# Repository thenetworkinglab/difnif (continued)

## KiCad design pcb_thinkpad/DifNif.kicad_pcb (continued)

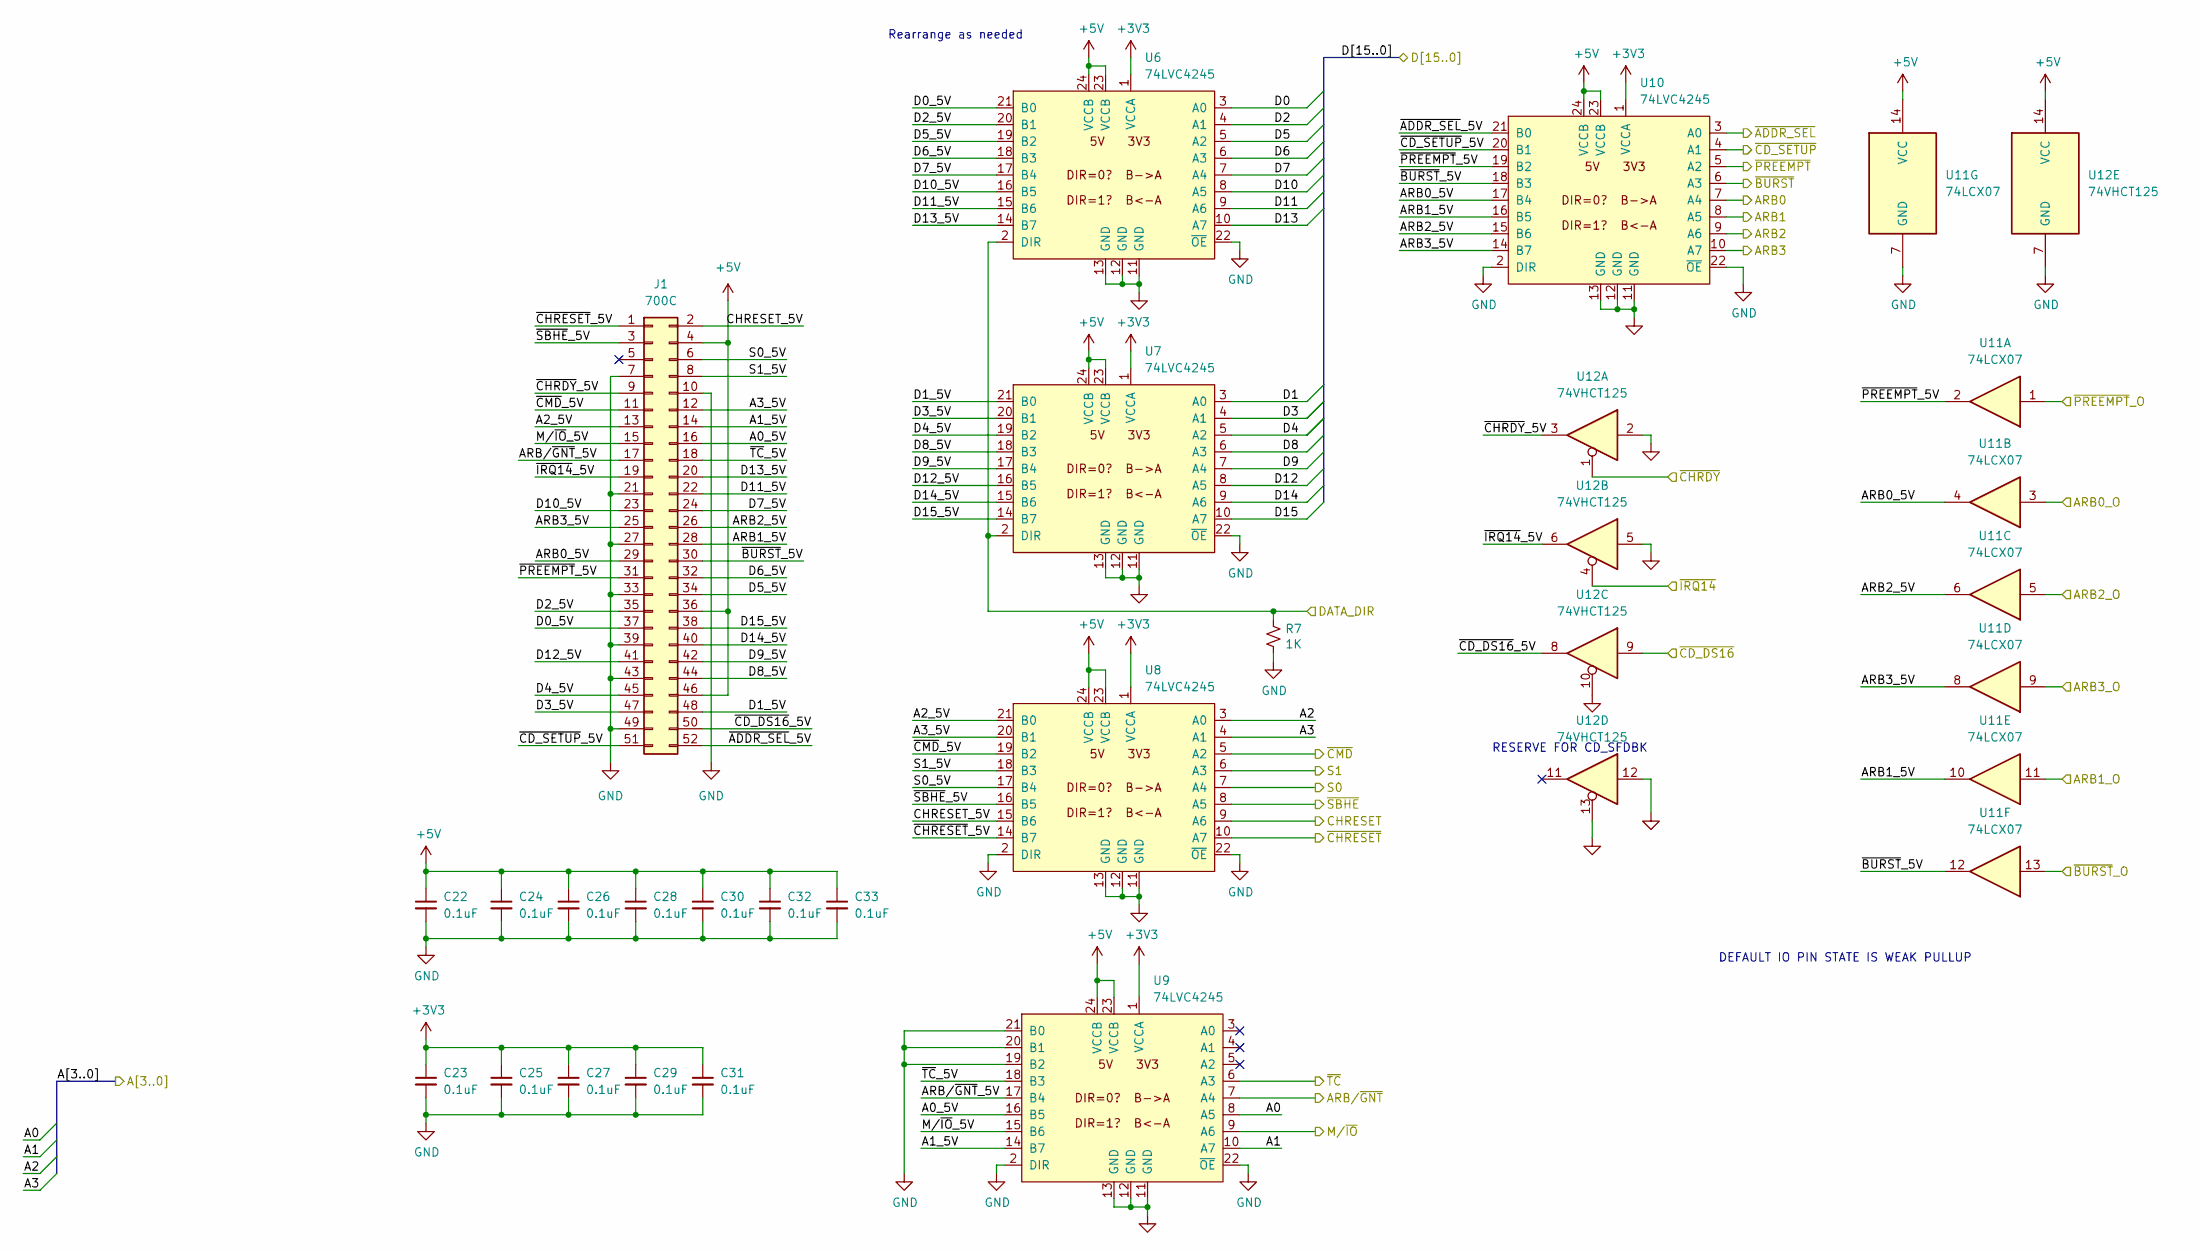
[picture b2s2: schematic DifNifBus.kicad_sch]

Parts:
C22, C23, C24, C25, C26, C27, C28, C29, C30, C31, C32, C33: 0.1uF; CAPC1608X100
J1: 700C; PinHeader_2x26_P2.00mm_Vertical
R7: 1K; RESC1608X55; Mouser 603-RC0603FR-071KL
U6, U7, U8, U9, U10: 74LVC4245; TSOP65P640X120-24; Mouser 771-74LVC4245APW-T
U11: 74LCX07; TSOP65P640X110-14; Mouser 757-74LCX07FTAE
U12: 74VHCT125; TSOP65P640X110-14; Mouser 757-74VHCT125AFT

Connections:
+3V3: C23.1, C25.1, C27.1, C29.1, C31.1, U6.1 (VCCA), U7.1 (VCCA), U8.1 (VCCA), U9.1 (VCCA), U10.1 (VCCA); also elsewhere on the board
+5V: C22.1, C24.1, C26.1, C28.1, C30.1, C32.1, C33.1, J1.4, J1.36, J1.46, U6.23 (VCCB), U6.24 (VCCB), U7.23 (VCCB), U7.24 (VCCB), U8.23 (VCCB), U8.24 (VCCB), U9.23 (VCCB), U9.24 (VCCB), U10.23 (VCCB), U10.24 (VCCB), U11.14 (VCC), U12.14 (VCC); also elsewhere on the board
/A0: U9.8 (A5); also elsewhere on the board
/A1: U9.10 (A7); also elsewhere on the board
/A2: U8.3 (A0); also elsewhere on the board
/A3: U8.4 (A1); also elsewhere on the board
/ARB0: U10.7 (A4); also elsewhere on the board
/ARB0_O: U11.3; also elsewhere on the board
/ARB1: U10.8 (A5); also elsewhere on the board
/ARB1_O: U11.11; also elsewhere on the board
/ARB2: U10.9 (A6); also elsewhere on the board
/ARB2_O: U11.5; also elsewhere on the board
/ARB3: U10.10 (A7); also elsewhere on the board
/ARB3_O: U11.9; also elsewhere on the board
/ARB/~GNT: U9.7 (A4); also elsewhere on the board
/CHRESET: U8.9 (A6); also elsewhere on the board
/D0: U6.3 (A0); also elsewhere on the board
/D1: U7.3 (A0); also elsewhere on the board
/D2: U6.4 (A1); also elsewhere on the board
/D3: U7.4 (A1); also elsewhere on the board
/D4: U7.5 (A2); also elsewhere on the board
/D5: U6.5 (A2); also elsewhere on the board
/D6: U6.6 (A3); also elsewhere on the board
/D7: U6.7 (A4); also elsewhere on the board
/D8: U7.6 (A3); also elsewhere on the board
/D9: U7.7 (A4); also elsewhere on the board
/D10: U6.8 (A5); also elsewhere on the board
/D11: U6.9 (A6); also elsewhere on the board
/D12: U7.8 (A5); also elsewhere on the board
/D13: U6.10 (A7); also elsewhere on the board
/D14: U7.9 (A6); also elsewhere on the board
/D15: U7.10 (A7); also elsewhere on the board
/DATA_DIR: R7.1, U6.2 (DIR), U7.2 (DIR); also elsewhere on the board
/DifNifBus/A0_5V: J1.16, U9.16 (B5)
/DifNifBus/A1_5V: J1.14, U9.14 (B7)
/DifNifBus/A2_5V: J1.13, U8.21 (B0)
/DifNifBus/A3_5V: J1.12, U8.20 (B1)
/DifNifBus/ARB0_5V: J1.29, U10.17 (B4), U11.4
/DifNifBus/ARB1_5V: J1.28, U10.16 (B5), U11.10
/DifNifBus/ARB2_5V: J1.26, U10.15 (B6), U11.6
/DifNifBus/ARB3_5V: J1.25, U10.14 (B7), U11.8
/DifNifBus/ARB/~GNT_5V: J1.17, U9.17 (B4)
/DifNifBus/CHRESET_5V: J1.2, U8.15 (B6)
/DifNifBus/D0_5V: J1.37, U6.21 (B0)
/DifNifBus/D1_5V: J1.48, U7.21 (B0)
/DifNifBus/D2_5V: J1.35, U6.20 (B1)
/DifNifBus/D3_5V: J1.47, U7.20 (B1)
/DifNifBus/D4_5V: J1.45, U7.19 (B2)
/DifNifBus/D5_5V: J1.34, U6.19 (B2)
/DifNifBus/D6_5V: J1.32, U6.18 (B3)
/DifNifBus/D7_5V: J1.24, U6.17 (B4)
/DifNifBus/D8_5V: J1.44, U7.18 (B3)
/DifNifBus/D9_5V: J1.42, U7.17 (B4)
/DifNifBus/D10_5V: J1.23, U6.16 (B5)
/DifNifBus/D11_5V: J1.22, U6.15 (B6)
/DifNifBus/D12_5V: J1.41, U7.16 (B5)
/DifNifBus/D13_5V: J1.20, U6.14 (B7)
/DifNifBus/D14_5V: J1.40, U7.15 (B6)
/DifNifBus/D15_5V: J1.38, U7.14 (B7)
/DifNifBus/M/~IO_5V: J1.15, U9.15 (B6)
/DifNifBus/S0_5V: J1.6, U8.17 (B4)
/DifNifBus/S1_5V: J1.8, U8.18 (B3)
/DifNifBus/~ADDR_SEL_5V: J1.52, U10.21 (B0)
/DifNifBus/~BURST_5V: J1.30, U10.18 (B3), U11.12
/DifNifBus/~CD_DS16_5V: J1.50, U12.8
/DifNifBus/~CD_SETUP_5V: J1.51, U10.20 (B1)
/DifNifBus/~CHRDY_5V: J1.9, U12.3
/DifNifBus/~CHRESET_5V: J1.1, U8.14 (B7)
/DifNifBus/~CMD_5V: J1.11, U8.19 (B2)
/DifNifBus/~IRQ14_5V: J1.19, U12.6
/DifNifBus/~PREEMPT_5V: J1.31, U10.19 (B2), U11.2
/DifNifBus/~SBHE_5V: J1.3, U8.16 (B5)
/DifNifBus/~TC_5V: J1.18, U9.18 (B3)
/M/~IO: U9.9 (A6); also elsewhere on the board
/S0: U8.7 (A4); also elsewhere on the board
/S1: U8.6 (A3); also elsewhere on the board
/~ADDR_SEL: U10.3 (A0); also elsewhere on the board
/~BURST: U10.6 (A3); also elsewhere on the board
/~BURST_O: U11.13; also elsewhere on the board
/~CD_DS16: U12.9; also elsewhere on the board
/~CD_SETUP: U10.4 (A1); also elsewhere on the board
/~CHRDY: U12.1; also elsewhere on the board
/~CHRESET: U8.10 (A7); also elsewhere on the board
/~CMD: U8.5 (A2); also elsewhere on the board
/~IRQ14: U12.4; also elsewhere on the board
/~PREEMPT: U10.5 (A2); also elsewhere on the board
/~PREEMPT_O: U11.1; also elsewhere on the board
/~SBHE: U8.8 (A5); also elsewhere on the board
/~TC: U9.6 (A3); also elsewhere on the board
GND: C22.2, C23.2, C24.2, C25.2, C26.2, C27.2, C28.2, C29.2, C30.2, C31.2, C32.2, C33.2, J1.7, J1.10, J1.21, J1.27, J1.33, J1.39, J1.43, J1.49, R7.2, U6.11 (GND), U6.12 (GND), U6.13 (GND), U6.22 (~OE), U7.11 (GND), U7.12 (GND), U7.13 (GND), U7.22 (~OE), U8.2 (DIR), U8.11 (GND), U8.12 (GND), U8.13 (GND), U8.22 (~OE), U9.2 (DIR), U9.11 (GND), U9.12 (GND), U9.13 (GND), U9.19 (B2), U9.20 (B1), U9.21 (B0), U9.22 (~OE), U10.2 (DIR), U10.11 (GND), U10.12 (GND), U10.13 (GND), U10.22 (~OE), U11.7 (GND), U12.2, U12.5, U12.7 (GND), U12.10, U12.12, U12.13; also elsewhere on the board

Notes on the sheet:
Rearrange as needed
RESERVE FOR CD_SFDBK
DEFAULT IO PIN STATE IS WEAK PULLUP

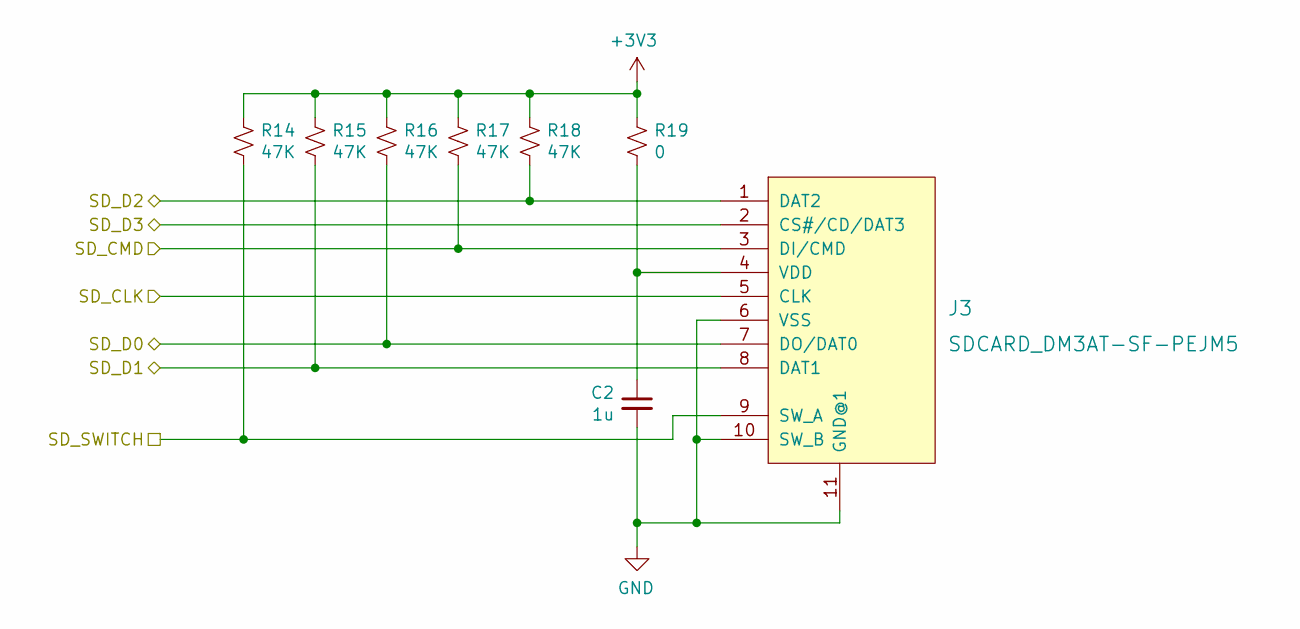
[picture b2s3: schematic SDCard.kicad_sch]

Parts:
C2: 1u; CAPC1608X100; Mouser 810-CGA3E1X7R1C105AC
J3: SDCARD_DM3AT-SF-PEJM5; microSD_HC_Hirose_DM3AT-SF-PEJM5; Mouser 798-DM3AT-SF-PEJM540
R14, R15, R16, R17, R18: 47K; RESC1608X55; Mouser 603-RC0603FR-0747KL
R19: 0; RESC2012X55; Mouser 603-RC0805FR-070RL

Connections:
+3V3: R14.1, R15.1, R16.1, R17.1, R18.1, R19.1; also elsewhere on the board
/SDCard/SD_SWITCH: J3.9 (SW_A), R14.2; also elsewhere on the board
/SD_CLK: J3.5 (CLK); also elsewhere on the board
/SD_CMD: J3.3 (DI/CMD), R17.2; also elsewhere on the board
/SD_D0: J3.7 (DO/DAT0), R16.2; also elsewhere on the board
/SD_D1: J3.8 (DAT1), R15.2; also elsewhere on the board
/SD_D2: J3.1 (DAT2), R18.2; also elsewhere on the board
/SD_D3: J3.2 (CS#/CD/DAT3); also elsewhere on the board
GND: C2.2, J3.6 (VSS), J3.10 (SW_B), J3.11 (GND@1); also elsewhere on the board
unnamed: C2.1, J3.4 (VDD), R19.2

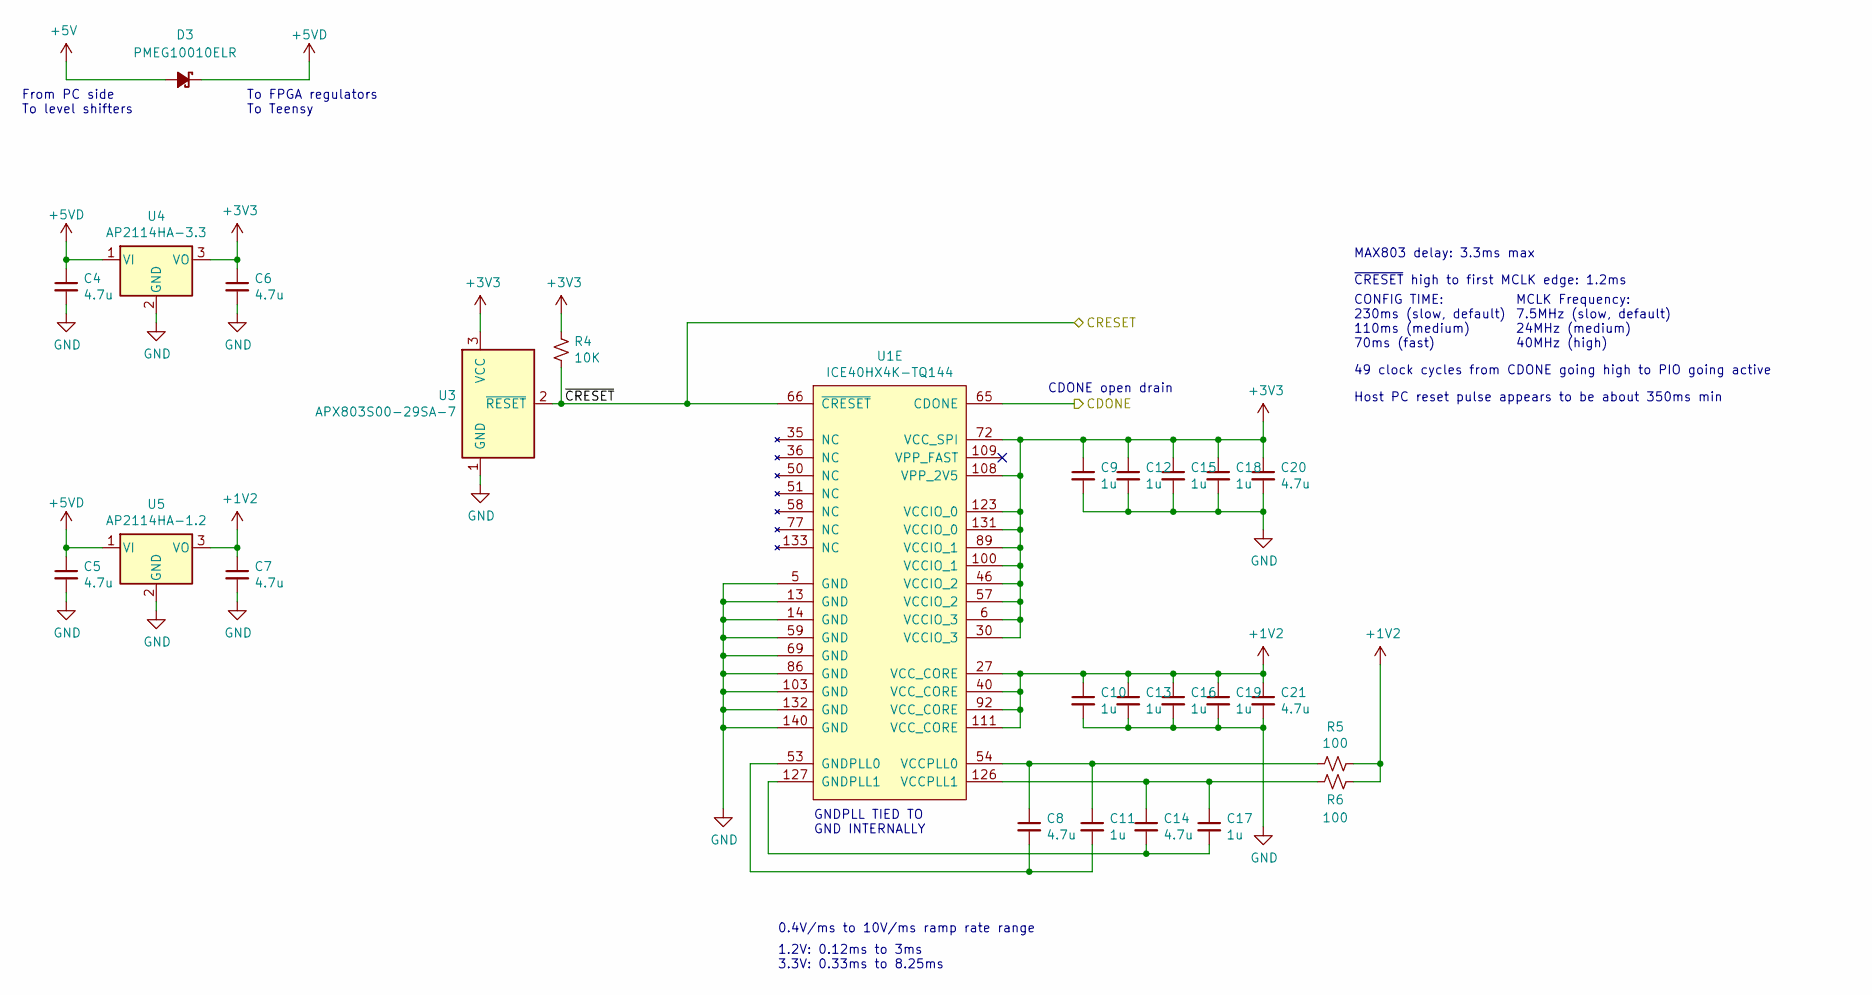
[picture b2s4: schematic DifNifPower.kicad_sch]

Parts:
C4, C5, C6, C7, C8, C14, C20, C21: 4.7u; CAPC1608X100; Mouser 187-CL10A475KP8NNNC
C9, C10, C11, C12, C13, C15, C16, C17, C18, C19: 1u; CAPC1608X100; Mouser 810-CGA3E1X7R1C105AC
D3: PMEG10010ELR; SOD3716X117; Mouser 771-PMEG10010ELRX
R4: 10K; RESC1608X55; Mouser 603-RC0603FR-0710KL
R5, R6: 100; RESC1608X55; Mouser 603-RC0603FR-07100RL
U1: ICE40HX4K-TQ144; TSQFP50P2200X2200X160-144; Mouser 842-ICE40HX4K-TQ144
U3: APX803S00-29SA-7; SOT95P230X117-3; Mouser 621-APX803S00-29SA-7
U4: AP2114HA-3.3; SOT230P700X170-3; Mouser 621-AP2114HA-3.3TRG1
U5: AP2114HA-1.2; SOT230P700X170-3; Mouser 621-AP2114HA-1.2TRG1

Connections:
+1V2: C7.1, C10.1, C13.1, C16.1, C19.1, C21.1, R5.1, R6.1, U1.27 (VCC_CORE), U1.40 (VCC_CORE), U1.92 (VCC_CORE), U1.111 (VCC_CORE), U5.3 (VO)
+3V3: C6.1, C9.1, C12.1, C15.1, C18.1, C20.1, R4.1, U1.6 (VCCIO_3), U1.30 (VCCIO_3), U1.46 (VCCIO_2), U1.57 (VCCIO_2), U1.72 (VCC_SPI), U1.89 (VCCIO_1), U1.100 (VCCIO_1), U1.108 (VPP_2V5), U1.123 (VCCIO_0), U1.131 (VCCIO_0), U3.3 (VCC), U4.3 (VO); also elsewhere on the board
+5V: D3.2 (A); also elsewhere on the board
+5VD: C4.1, C5.1, D3.1 (K), U4.1 (VI), U5.1 (VI); also elsewhere on the board
/CDONE: U1.65 (CDONE); also elsewhere on the board
/~CRESET: R4.2, U1.66 (~CRESET), U3.2 (~RESET); also elsewhere on the board
GND: C4.2, C5.2, C6.2, C7.2, C9.2, C10.2, C12.2, C13.2, C15.2, C16.2, C18.2, C19.2, C20.2, C21.2, U1.5 (GND), U1.13 (GND), U1.14 (GND), U1.59 (GND), U1.69 (GND), U1.86 (GND), U1.103 (GND), U1.132 (GND), U1.140 (GND), U3.1 (GND), U4.2 (GND), U5.2 (GND); also elsewhere on the board
unnamed: C8.1, C11.1, R5.2, U1.54 (VCCPLL0)
unnamed: C8.2, C11.2, U1.53 (GNDPLL0)
unnamed: C14.1, C17.1, R6.2, U1.126 (VCCPLL1)
unnamed: C14.2, C17.2, U1.127 (GNDPLL1)

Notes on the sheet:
49 clock cycles from CDONE going high to PIO going active
Host PC reset pulse appears to be about 350ms min
To FPGA regulators To Teensy
CONFIG TIME: 230ms (slow, default) 110ms (medium) 70ms (fast)
MCLK Frequency: 7.5MHz (slow, default) 24MHz (medium) 40MHz (high)
CDONE open drain
GNDPLL TIED TO GND INTERNALLY
From PC side To level shifters
0.4V/ms to 10V/ms ramp rate range
1.2V: 0.12ms to 3ms 3.3V: 0.33ms to 8.25ms
~{CRESET} high to first MCLK edge: 1.2ms
MAX803 delay: 3.3ms max

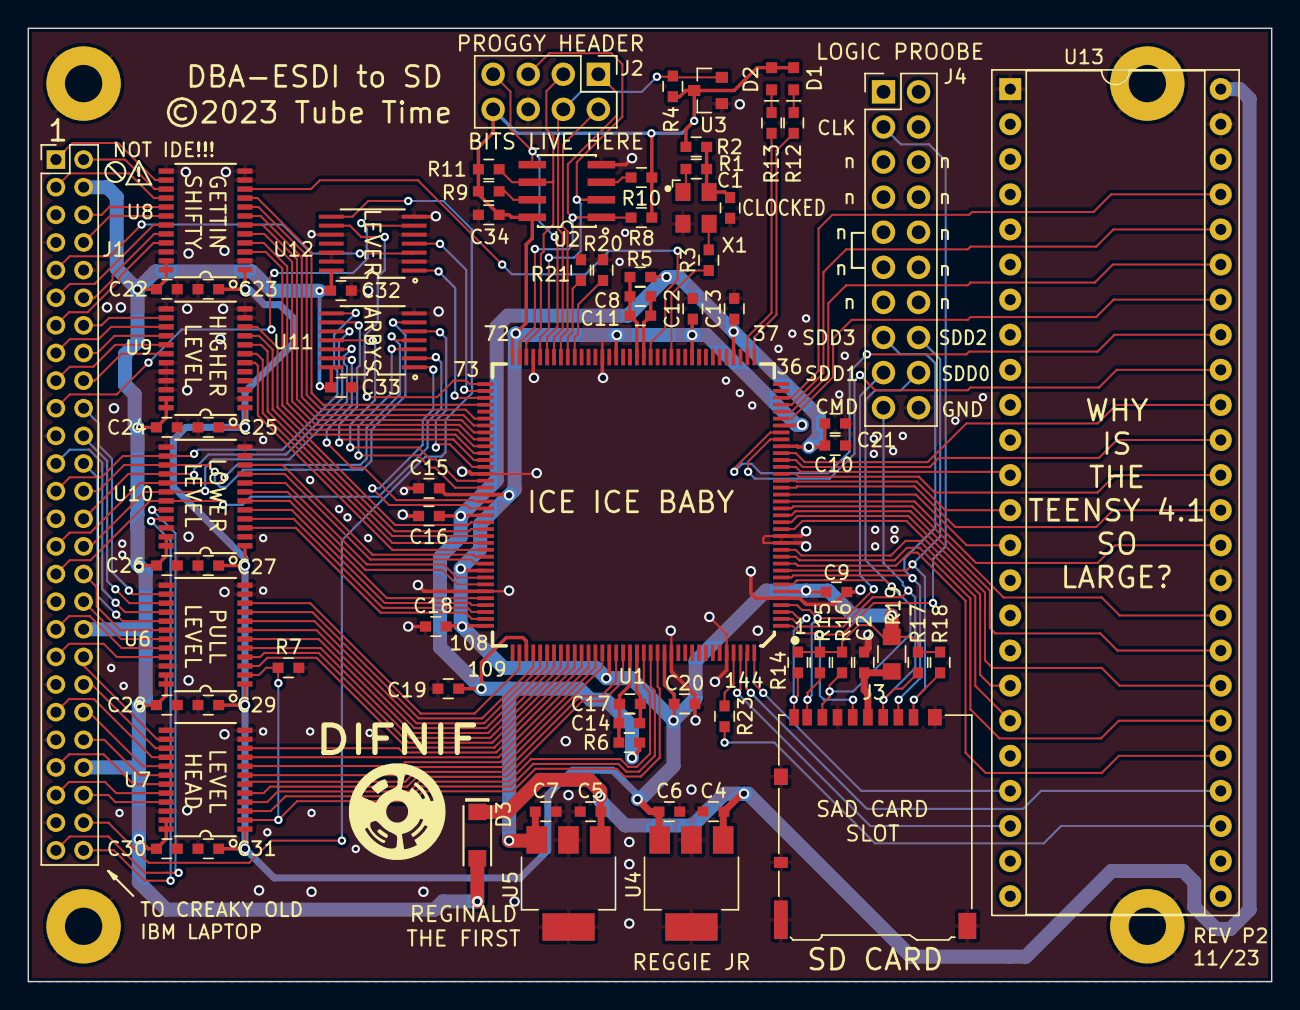
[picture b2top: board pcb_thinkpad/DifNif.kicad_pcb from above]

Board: 2 copper layers, 90.0 x 69.0 mm, 80 parts (0 on the bottom side), 148 nets.

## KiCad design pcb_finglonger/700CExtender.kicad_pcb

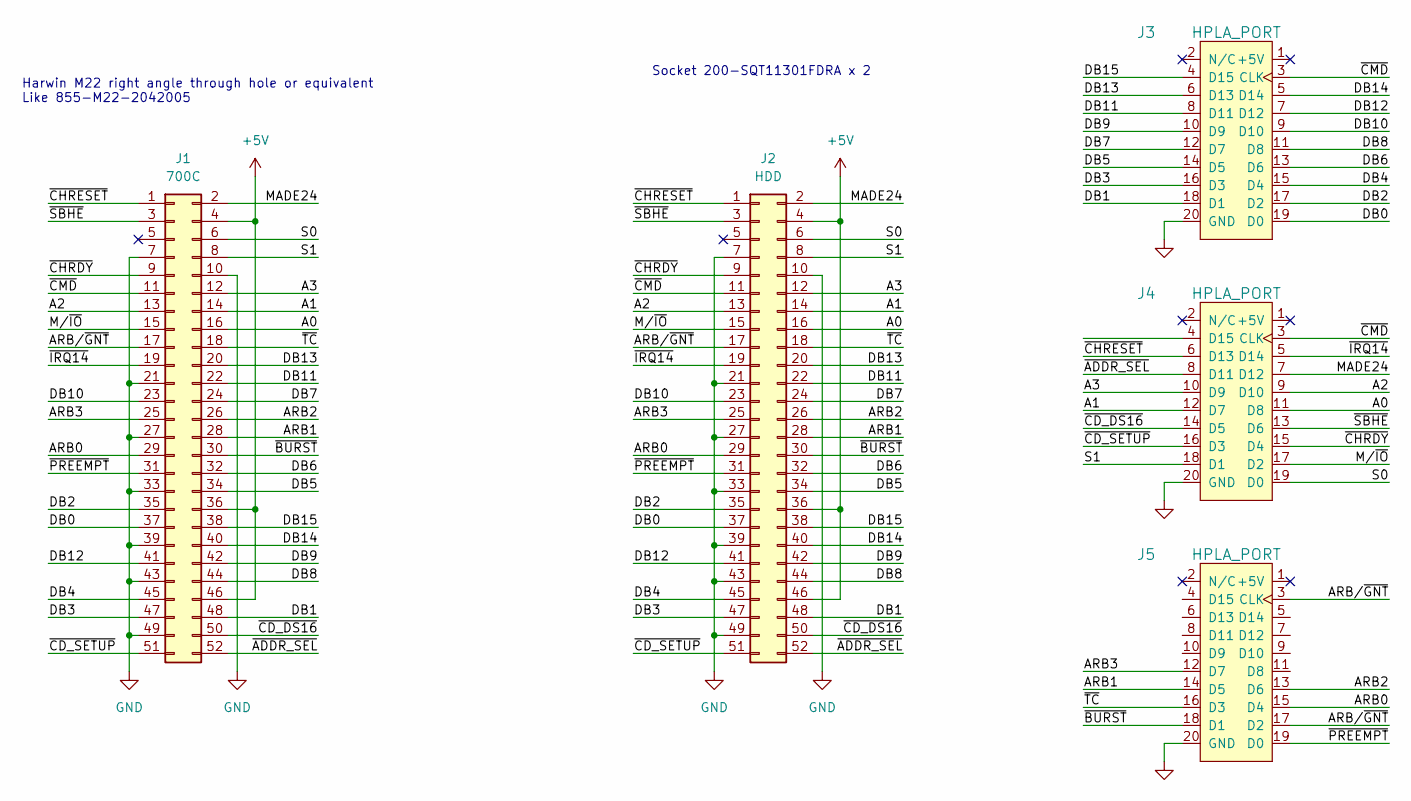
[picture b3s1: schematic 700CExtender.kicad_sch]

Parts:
J1: 700C; PinHeader_2x26_P2.00mm_Vertical
J2: HDD; PinSocket_2x26_P2.00mm_Vertical
J3, J4, J5: HPLA_PORT; PinHeader_2x10_P2.54mm_Vertical

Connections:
+5V: J1.4, J1.36, J1.46, J2.4, J2.36, J2.46
/A0: J1.16, J2.16, J4.11 (D8)
/A1: J1.14, J2.14, J4.12 (D7)
/A2: J1.13, J2.13, J4.9 (D10)
/A3: J1.12, J2.12, J4.10 (D9)
/ARB0: J1.29, J2.29, J5.15 (D4)
/ARB1: J1.28, J2.28, J5.14 (D5)
/ARB2: J1.26, J2.26, J5.13 (D6)
/ARB3: J1.25, J2.25, J5.12 (D7)
/ARB/~GNT: J1.17, J2.17, J5.3 (CLK), J5.17 (D2)
/DB0: J1.37, J2.37, J3.19 (D0)
/DB1: J1.48, J2.48, J3.18 (D1)
/DB2: J1.35, J2.35, J3.17 (D2)
/DB3: J1.47, J2.47, J3.16 (D3)
/DB4: J1.45, J2.45, J3.15 (D4)
/DB5: J1.34, J2.34, J3.14 (D5)
/DB6: J1.32, J2.32, J3.13 (D6)
/DB7: J1.24, J2.24, J3.12 (D7)
/DB8: J1.44, J2.44, J3.11 (D8)
/DB9: J1.42, J2.42, J3.10 (D9)
/DB10: J1.23, J2.23, J3.9 (D10)
/DB11: J1.22, J2.22, J3.8 (D11)
/DB12: J1.41, J2.41, J3.7 (D12)
/DB13: J1.20, J2.20, J3.6 (D13)
/DB14: J1.40, J2.40, J3.5 (D14)
/DB15: J1.38, J2.38, J3.4 (D15)
/MADE24: J1.2, J2.2, J4.7 (D12)
/M/~IO: J1.15, J2.15, J4.17 (D2)
/S0: J1.6, J2.6, J4.19 (D0)
/S1: J1.8, J2.8, J4.18 (D1)
/~ADDR_SEL: J1.52, J2.52, J4.8 (D11)
/~BURST: J1.30, J2.30, J5.18 (D1)
/~CD_DS16: J1.50, J2.50, J4.14 (D5)
/~CD_SETUP: J1.51, J2.51, J4.16 (D3)
/~CHRDY: J1.9, J2.9, J4.15 (D4)
/~CHRESET: J1.1, J2.1, J4.6 (D13)
/~CMD: J1.11, J2.11, J3.3 (CLK), J4.3 (CLK)
/~IRQ14: J1.19, J2.19, J4.5 (D14)
/~PREEMPT: J1.31, J2.31, J5.19 (D0)
/~SBHE: J1.3, J2.3, J4.13 (D6)
/~TC: J1.18, J2.18, J5.16 (D3)
GND: J1.7, J1.10, J1.21, J1.27, J1.33, J1.39, J1.43, J1.49, J2.7, J2.10, J2.21, J2.27, J2.33, J2.39, J2.43, J2.49, J3.20 (GND), J4.20 (GND), J5.20 (GND)

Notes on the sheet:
Harwin M22 right angle through hole or equivalent Like 855-M22-2042005
Socket 200-SQT11301FDRA x 2

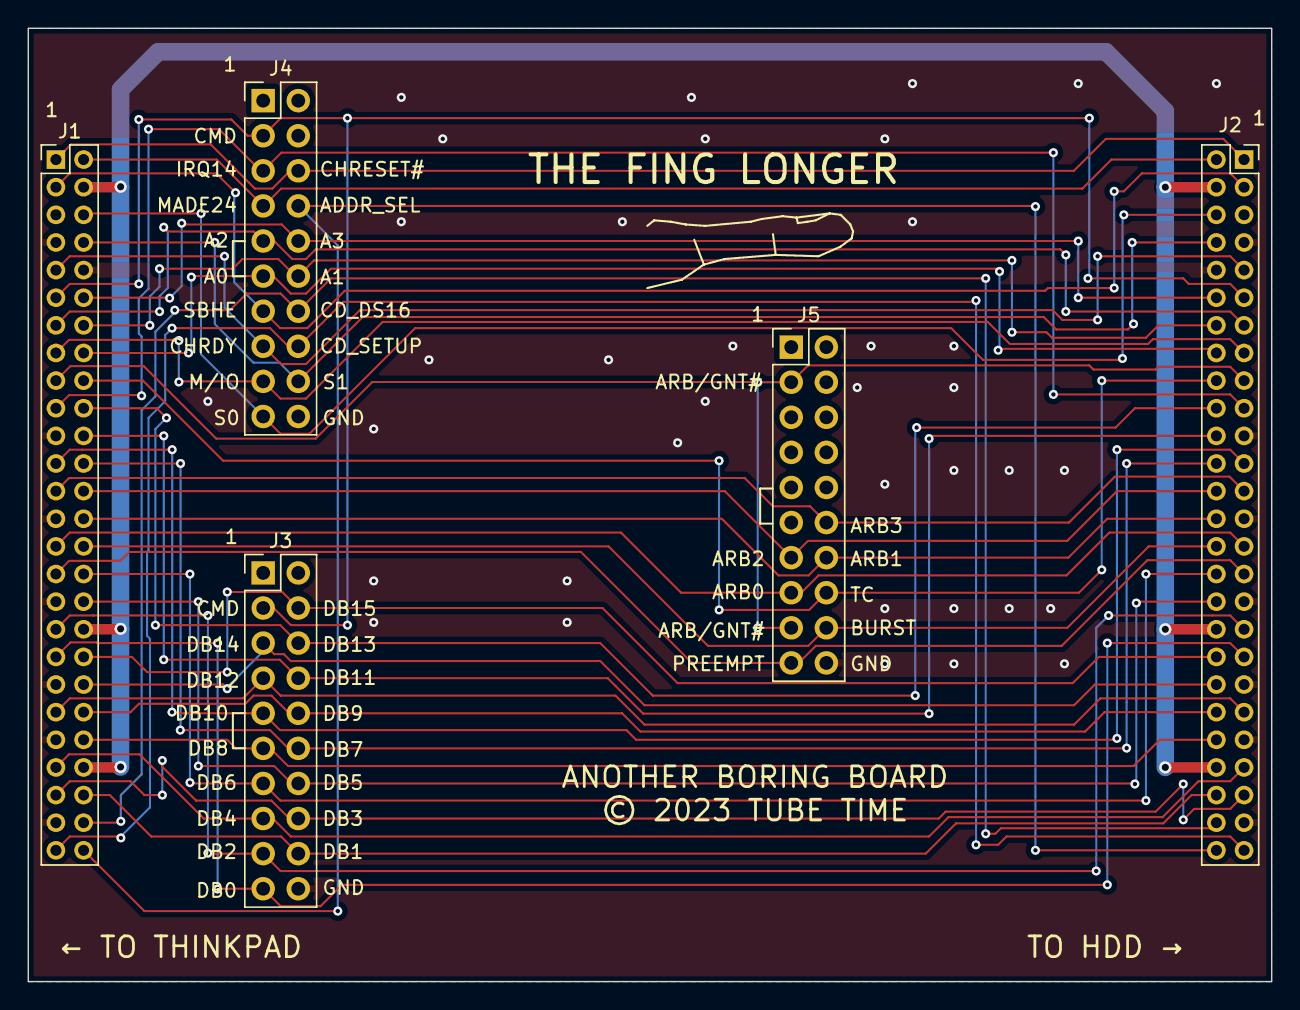
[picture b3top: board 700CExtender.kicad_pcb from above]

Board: 2 copper layers, 90.0 x 69.0 mm, 5 parts (0 on the bottom side), 42 nets.

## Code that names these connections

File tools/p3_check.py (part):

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Exports both boards' netlists with kicad-cli, then checks:
- every Rev P2 net the change shouldn't touch is unchanged in Rev P3;
- every new connection (docs/rev-p3-design.md) is there.
Parts are found by value and pin name (RP2040:GPIO8), or by reference
for Rev P2's (U1.33).

This file is part of a fork of DifNif; CERN-OHL-S-2.0.
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    b1, b2 = SWITCH[p]
    b.same(f'{r}.{b1}', fpga)
    b.same(f'{r}.{b2}', rp)
    b.same(f'{r}.1', 'RP2040:GPIO11')


def main():
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            b.fail(f'{r} still there')

    # FPGA <-> RP2040
    b.same('U1.26', 'RP2040:GPIO0')         # UART0 TX -> uart_rx
    b.same('U1.25', 'RP2040:GPIO1')         # uart_tx -> UART0 RX
    b.via('33', 'U1.70', 'RP2040:GPIO2')    # config flash SCK
    b.same('U1.70', 'U2.6')
    b.via('33', 'U1.67', 'RP2040:GPIO3')    # COPI
    b.same('U1.67', 'U2.5')
    b.same('U1.68', 'RP2040:GPIO4', 'U2.2')  # CIPO
    b.via('33', 'U1.71', 'RP2040:GPIO5')    # CS
    b.same('U1.71', 'U2.1')
    b.same('U1.66', 'RP2040:GPIO6', 'U3.2', 'J2.4')    # CRESET
    b.same('U1.65', 'RP2040:GPIO7', 'J2.2')            # CDONE
    b.same('U1.33', 'RP2040:GPIO8')         # sd_req
    b.same('U1.34', 'RP2040:GPIO9')         # sd_rel
    b.same('U1.31', 'RP2040:GPIO10')        # pfail
    b.via('10K', 'RP2040:GPIO11', 'U1.5')   # switch select, pulled to the FPGA side
    b.same('RP2040:GPIO12', 'J3.9', 'U1.3')  # card detect
    # the SD card through the switches
    for card, fpga, gp in (('J3.5', 'U1.1', 16), ('J3.3', 'U1.2', 17), ('J3.7', 'U1.7', 18),
                           ('J3.8', 'U1.4', 19), ('J3.1', 'U1.9', 20), ('J3.2', 'U1.8', 21)):
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    b.via('10K', 'RP2040:RUN', 'U1.6')
    for pin, fn in (('2', 'SWCLK'), ('4', 'SWD'), ('5', 'RUN')):
        b.same(f'SWD (not fitted).{pin}', f'RP2040:{fn}')
    led = b.via('330', 'RP2040:GPIO25', 'GRN:A')
    b.same('GRN:K', 'U1.5')
    b.same('D3.2', 'J1.a7')                 # the edge's +5V (D3's anode)
    b.via('10K', 'RP2040:GPIO26_ADC0', 'D3.2')
    b.via('15K', 'RP2040:GPIO26_ADC0', 'U1.5')
    b.via('10K', 'RP2040:GPIO22', 'USB_C.A4')  # VBUS detect
    b.via('15K', 'RP2040:GPIO22', 'U1.5')
    # USB and power
    b.via('27', 'RP2040:USB_DP', 'USB_C.A6')
    b.via('27', 'RP2040:USB_DM', 'USB_C.A7')
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            pcf[w[1]] = w[0]
    for pin, sig in sorted(pcf.items(), key=lambda x: int(x[0])):
        if sig == 'addr_sel_in_l':
            continue    # unconnected on the 72-pin boards: FULLADDR (R22) decodes on the card
        if len(b.nets[b.net(f'U1.{pin}')]) < 2:
            b.fail(f'pcf {sig} on pin {pin}, which goes nowhere')
    teensy = {p for name, n in p2.nets.items() if name.startswith('/TN') or 'IOT_219' in name
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
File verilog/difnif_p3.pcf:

# Rev P3 (docs/rev-p3-spec.md): Rev P2's pins without the Teensy, plus the
# RP2040 link, the QSPI PSRAM, U7's own direction line and test points.
# The new signals use pins the Teensy freed on the FPGA's left side (bank 3),
# next to the SD card's; data_dir_hi sits beside data_dir (130).

### icetest

### Copyright (c) 2021 Eric Schlaepfer
### This work is licensed under CERN-OHL-S-2.0.

### Clock
set_io clk_10m      49

### Micro Channel bus
set_io chreset_l    52 # Probably not actually chreset_l!

set_io cd_ds16_l    73
set_io irq14_l      74
set_io cd_chrdy_l   75
set_io chreset      76
set_io sbhe_l       78
set_io s0_w_l       79
set_io s1_r_l       80
set_io cmd_l        81
set_io bus_a[3]     82
set_io bus_a[2]     83
set_io arb_o[3]     84
set_io arb_o[2]     85
set_io arb_o[1]     87
set_io arb_o[0]     88
set_io burst_o_l    90
set_io preempt_o_l  91
set_io bus_a[1]     93
set_io m_io_l       94
set_io bus_a[0]     95
set_io arb_gnt_l    96
set_io tc_l         97
set_io arb[3]       98
set_io arb[2]       99
set_io arb[1]       101
set_io arb[0]       102
set_io burst_l      104
set_io preempt_l    105
set_io cd_setup_l   106
set_io addr_sel_in_l 107
set_io bus_d[13]    110
set_io bus_d[11]    112
set_io bus_d[10]    113
set_io bus_d[7]     114
set_io bus_d[6]     115
set_io bus_d[5]     116
set_io bus_d[2]     117
set_io bus_d[0]     118
set_io bus_d[15]    119
set_io bus_d[14]    120
set_io bus_d[12]    121
set_io bus_d[9]     122
set_io bus_d[8]     124
set_io bus_d[4]     125
set_io bus_d[3]     128
set_io bus_d[1]     129
set_io data_dir     130

# Extended address lines
# 72-pin interface only
set_io bus_a[4]     39
set_io bus_a[5]     41
set_io bus_a[6]     42
set_io bus_a[7]     43
set_io bus_a[8]     44
set_io bus_a[9]     45
set_io bus_a[10]    47
set_io bus_a[11]    48
set_io bus_a[12]    55
set_io bus_a[13]    56
set_io bus_a[14]    60
set_io bus_a[15]    61

set_io fulladdr_l   62

# Card selected feedback, 72-pin only. Needs Rev P2: drives the input of the
# spare 74VHCT125 section (U12 pin 12, /OE grounded), push-pull to J1 B08.
# Pin 134 is unconnected on Rev P1.
set_io cd_sfdbk_l   134

### Teensy connections
# Data port (bidirectional)

# Address pins

# Control pins

# Spares

### LEDs
set_io led0         37
set_io led1         38

### SD card
set_io sd_clk       1
set_io sd_cmd       2
set_io sd_switch    3
set_io sd_d[1]      4
set_io sd_d[0]      7
set_io sd_d[3]      8
set_io sd_d[2]      9

# Rev P3 additions
set_io data_dir_hi  135
set_io uart_tx      25
set_io uart_rx      26
set_io sd_req       33
set_io sd_rel       34
set_io pfail        31
set_io ps_clk       17
set_io ps_cs_l      18
set_io ps_d[0]      21
set_io ps_d[1]      23
set_io ps_d[2]      28
set_io ps_d[3]      29
set_io tp[0]        32
set_io tp[1]        11
set_io tp[2]        12
set_io tp[3]        16

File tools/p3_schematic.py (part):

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# The Teensy's FPGA pins (by their Rev P2 labels) on Rev P3; see
# verilog/difnif_p3.pcf. Labels not listed here are unused pins.
TN_RENAME = {
    'TN16': 'FPGA_TX',    # 25 uart_tx -> RP2040 GPIO1
    'TN17': 'FPGA_RX',    # 26 uart_rx <- RP2040 GPIO0
    'TN22': 'SD_REQ',     # 33
    'TN23': 'SD_REL',     # 34
    'TN20': 'PFAIL',      # 31
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def edit_bus(bus, path, insts):
    """U6 keeps DATA_DIR; U7 moves to DATA_DIR_HI"""
    sh = Sheet(bus, path, insts)
    g = next(g for g in S.groups(bus) if any(l[1] == 'DATA_DIR' for l in g['labels']))
    pins = {S.ref(s): p for s, n, p in g['pins']}
    u6, u7 = pins['U6'], pins['U7']
    keep = []
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        pts = [(S.r(x[1]), S.r(x[2])) for x in K.find(K.first(w, 'pts'), 'xy')]
        if u6 in pts or u7 in pts or pins['R7'] in pts:
            keep.append(w)
    hl = next(l for l in g['labels'] if l[1] == 'DATA_DIR')
    hp = (S.r(K.first(hl, 'at')[1]), S.r(K.first(hl, 'at')[2]))
    for w in g['wires']:
        pts = [(S.r(x[1]), S.r(x[2])) for x in K.find(K.first(w, 'pts'), 'xy')]
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        for pin in (u6, u7):
            if pin in pts:
                stub[pin] = pts[1] if pts[0] == pin else pts[0]
    sh.label(stub[u6], (-1, 0), 'DATA_DIR')
    sh.label(stub[u7], (-1, 0), 'DATA_DIR_HI', 'global')


def edit_sd(sd, path, insts, ref):
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            hl[:] = ['label', Str('CARD_' + name[3:]), at,
                     ['effects', font(), ['justify', side, 'bottom']], K.first(hl, 'uuid')]
    # card detect to the RP2040 too: tap the long wire of SD_SWITCH
    g = next(g for g in S.groups(sd) if any(l[1] == 'SD_SWITCH' for l in g['labels']))
    w = max(g['wires'], key=lambda w: abs(float(K.first(w, 'pts')[1][1]) - float(K.first(w, 'pts')[2][1])))  # longest along X
    a, b = K.first(w, 'pts')[1], K.first(w, 'pts')[2]
    assert a[2] == b[2]
    mid = (S.r(round((float(a[1]) + float(b[1])) / 2 / 2.54) * 2.54), S.r(a[2]))
    sh.label(mid, (0, 1), 'SD_CD', 'global')

    chans = [lines[:4], lines[4:] + [None, None]]
    units = [(1, '4', '2', '3'), (2, '7', '5', '6'), (3, '9', '11', '10'), (4, '12', '14', '13')]
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        '56': 'QSPI_SS', '53': 'QSPI_SD0', '55': 'QSPI_SD1', '54': 'QSPI_SD2',
        '51': 'QSPI_SD3', '52': 'QSPI_SCLK',
        '20': 'XIN', '21': 'XOUT', '24': 'SWCLK', '25': 'SWDIO',
        '2': 'g:FPGA_RX', '3': 'g:FPGA_TX',             # GPIO0 UART0 TX, GPIO1 UART0 RX
        '4': ('RP_SCK', 17.78), '5': ('RP_COPI', 17.78), '6': 'g:SPI_CIPO', '7': ('RP_CS', 17.78),
        '8': 'g:~{CRESET}', '9': 'g:CDONE',
        '11': 'g:SD_REQ', '12': 'g:SD_REL', '13': 'g:PFAIL', '14': 'g:SD_SEL', '15': 'g:SD_CD',
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
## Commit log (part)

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2023-07-29 Initial version
2023-07-29 Updated PCF
2023-07-29 PCF mods, add first test bench
2023-07-29 Fix test bench issues
2023-07-29 Add a few files to gitignore
2023-08-01 Start of basic read transfer
2023-08-10 last checkin for sync mode
2023-08-10 async implementation
2023-08-15 add data byte steering
2023-08-15 16-bit transfers in test bench
2023-08-16 fix burst_o_l being held low
2023-08-18 remove made24, add chreset
2023-08-18 refactoring
2023-08-18 start implementing flags
2023-08-23 initial teensy port
2023-08-23 add teensy sketch and interface with test reg
2023-08-23 gitignore update
2023-08-30 register access from MCA to Teensy works!
2023-09-03 added ISR reg
2023-09-04 MCA bus highlighting for gtkwave
2023-09-04 add cifr and sifr
2023-09-04 add flag bits and interrupt
2023-09-04 implement some command structure
2023-09-23 Hook up interrupt output
2023-09-24 improve host interface
2023-09-24 get rid of extra pending flag. add some tests.
2023-09-24 fix SIFR mailbox glitches
2023-09-24 hardware triggered busy bit
2023-09-26 fix ATN mailbox
2023-09-26 ISR mailbox fixes
2023-09-26 fix CIFR double read issue
2023-09-27 add data register and tranfer request flag
2023-09-28 attach buffer cmds and read sector!
2023-09-29 add clear flag function
2023-09-29 fix interrupt behavior
2023-09-29 add POS information cmd, POS regs
2023-09-30 initial (broken) dma
    Read DMA sometimes works. Write DMA freezes the machine.
2023-10-03 fix la_dma_selected holding too long during write dma cycle
2023-10-04 DMA (non burst) working.
2023-10-05 add hard reset. code cleanup.
2023-10-05 Add most remaining commands
2023-10-07 read-only disk image support
2023-10-07 Enable POS registers
2023-10-07 Pseudo RBA, log spurious EOI
2023-10-08 Implemented pseudo RBAs. It boots now!
2023-10-08 stubbed out write routine
2023-10-17 Add 1C cmd variant. Fix write off-by-two error
2023-10-17 test output for ATN flag testing
2023-10-19 fix atn flag clock domain crossing issue
2023-10-19 fix SIFR and CIFR mailbox issues
2023-10-19 data register flag tidy up
2023-10-20 speedup Teensy to FPGA interface
2023-10-20 Add synch clock line to Teensy interface
2023-11-10 Enable standalone operation
2023-11-10 Rearrange verilog location
2023-11-10 Add PCB files
2023-11-10 add initial difdiag
2023-11-11 Added 72-pin form factor board
2023-11-11 Add diode OR, add clock series R
2023-11-28 fix non-POS IO when card disabled. test bench tweaks
2023-11-28 fix rare dma glitch
2023-11-28 fabout form factor pcb
2023-12-02 Support 72-pin form factor
2023-12-17 potential fix for bad sector writes
2023-12-17 difdiag: add int13h tests
2026-01-27 add POS bypass mode
2026-01-27 Readme, docs, update license
2026-01-27 Bug list
